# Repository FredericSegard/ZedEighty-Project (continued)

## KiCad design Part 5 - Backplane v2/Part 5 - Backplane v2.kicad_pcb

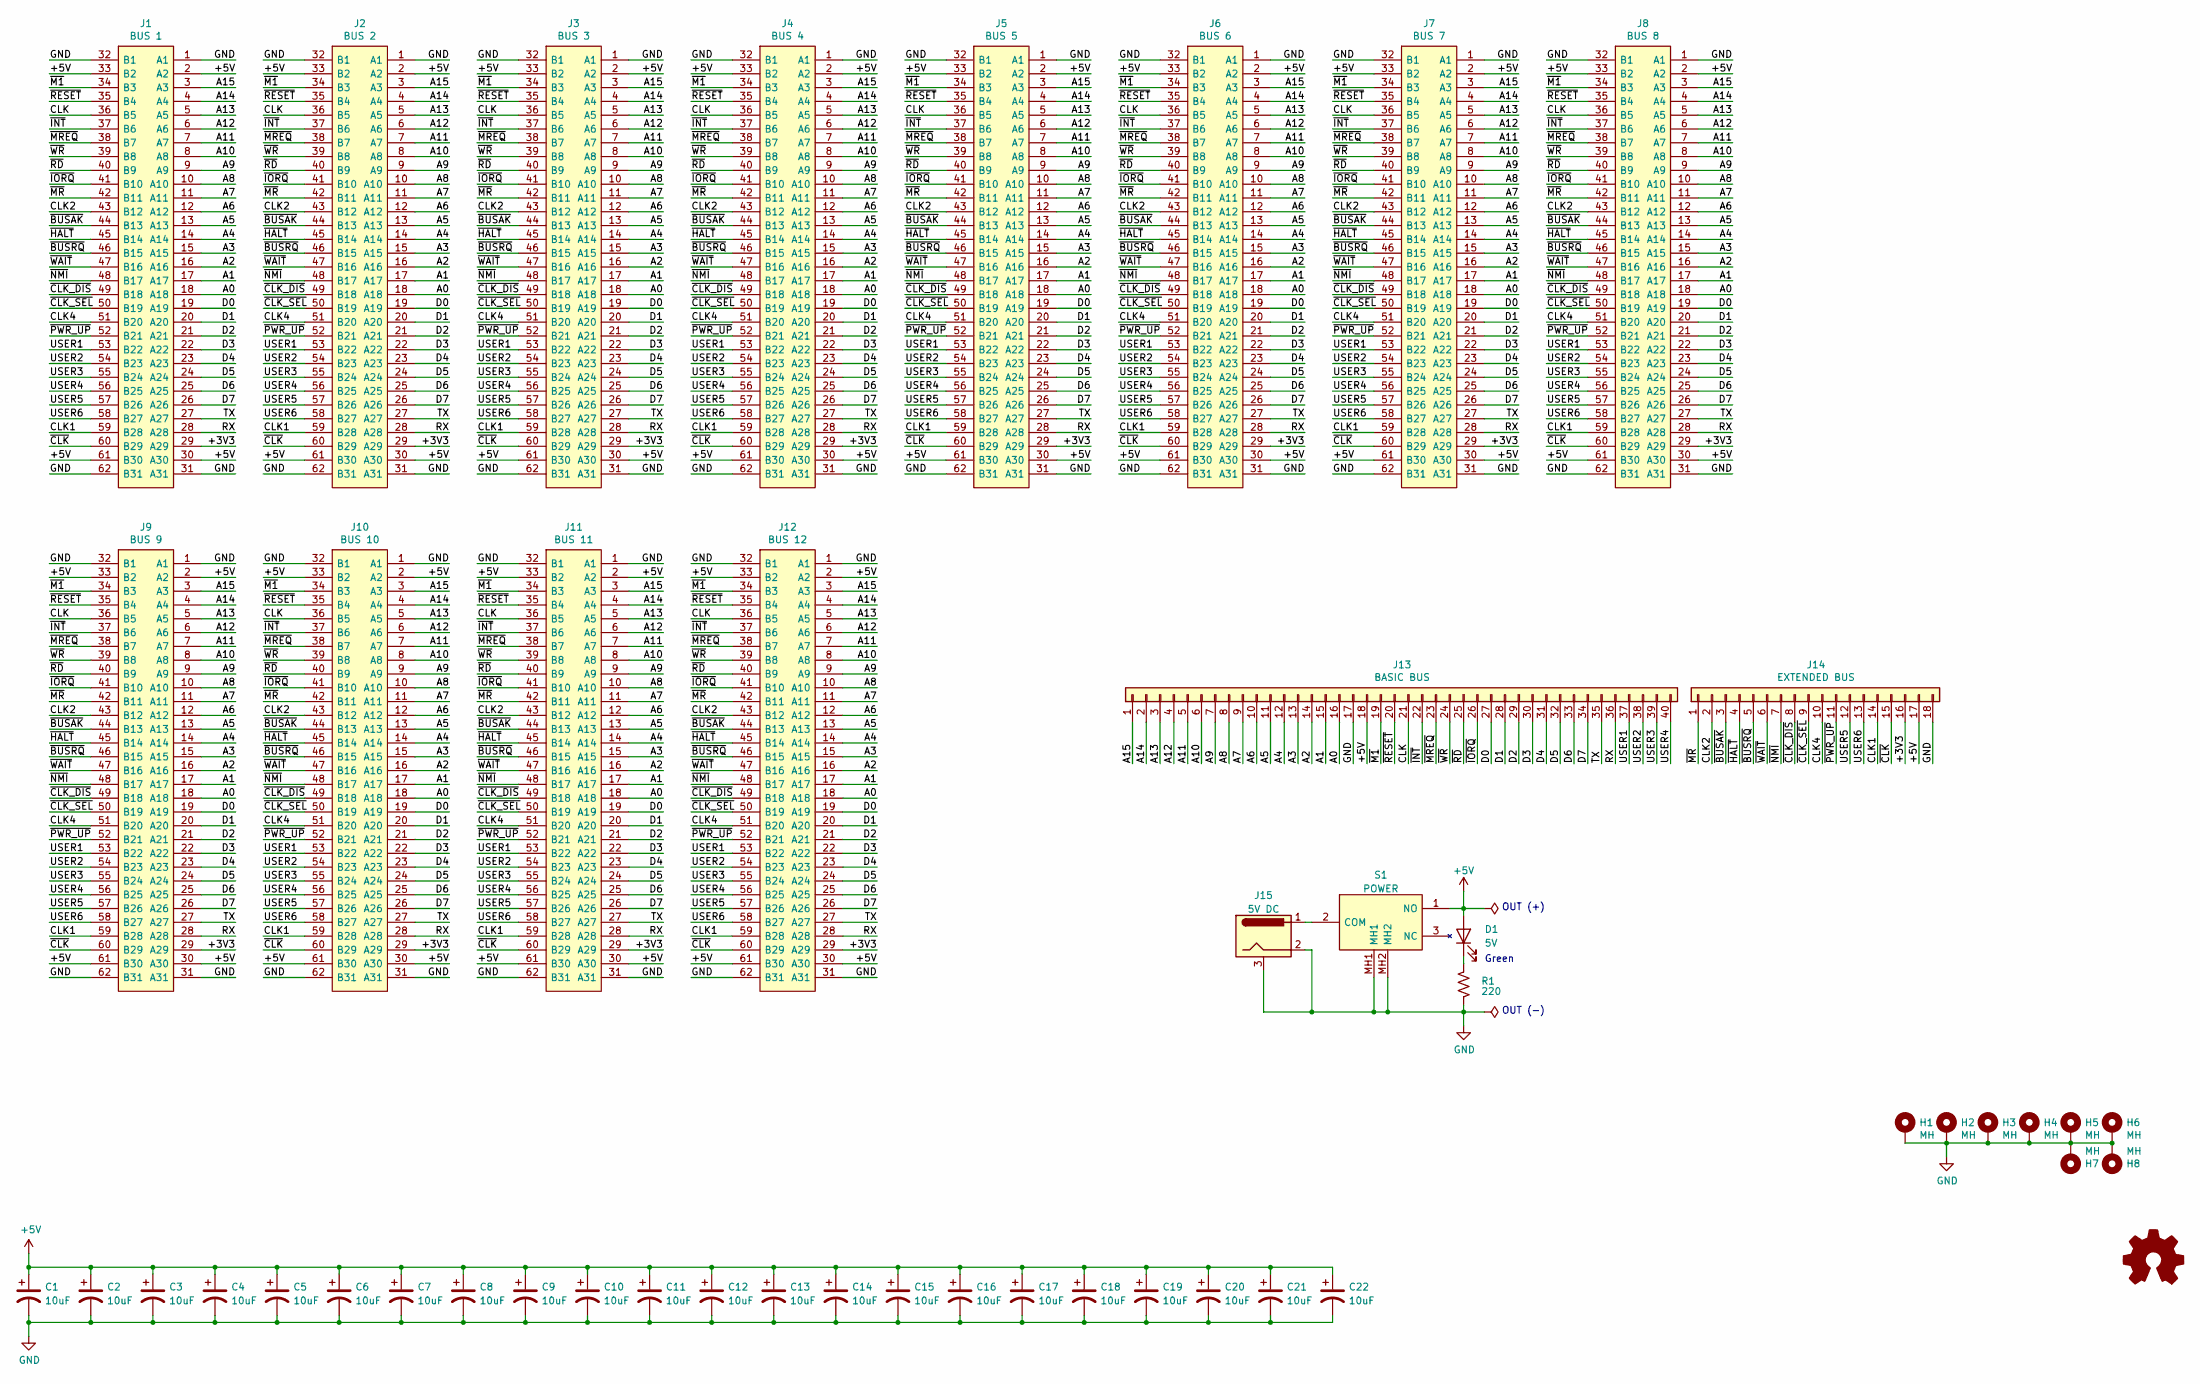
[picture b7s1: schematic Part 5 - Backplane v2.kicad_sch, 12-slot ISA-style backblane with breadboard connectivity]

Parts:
C1, C2, C3, C4, C5, C6, C7, C8, C9, C10, C11, C12, C13, C14, C15, C16, C17, C18, C19, C20, C21, C22: 10uF; CP_Radial_D6.3mm_P2.50mm
D1: 5V; LED_D3.0mm
H1, H2, H3, H4, H5, H6, H7, H8: MH; MountingHole_3.2mm_M3_Pad_Via
J1: BUS 1; ISA_Connector; Mouser Part Number 571-6-5530843-5
J2: BUS 2; ISA_Connector; Mouser Part Number 571-6-5530843-5
J3: BUS 3; ISA_Connector; Mouser Part Number 571-6-5530843-5
J4: BUS 4; ISA_Connector; Mouser Part Number 571-6-5530843-5
J5: BUS 5; ISA_Connector; Mouser Part Number 571-6-5530843-5
J6: BUS 6; ISA_Connector; Mouser Part Number 571-6-5530843-5
J7: BUS 7; ISA_Connector; Mouser Part Number 571-6-5530843-5
J8: BUS 8; ISA_Connector; Mouser Part Number 571-6-5530843-5
J9: BUS 9; ISA_Connector; Mouser Part Number 571-6-5530843-5
J10: BUS 10; ISA_Connector; Mouser Part Number 571-6-5530843-5
J11: BUS 11; ISA_Connector; Mouser Part Number 571-6-5530843-5
J12: BUS 12; ISA_Connector; Mouser Part Number 571-6-5530843-5
J13: BASIC BUS; PinHeader_1x40_P2.54mm_Vertical
J14: EXTENDED BUS; PinHeader_1x18_P2.54mm_Vertical
J15: 5V DC; BarrelJack_Horizontal
R1: 220; R_Axial_DIN0207_L6.3mm_D2.5mm_P10.16mm_Horizontal
S1: POWER; SPDT_NKK_SWITCH_M2012S2A2W30; Manufacturer_Part_Number M2012S2A2W30; Mouser Part Number 633-M2012S2A2W30

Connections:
+5V: C1.1, C2.1, C3.1, C4.1, C5.1, C6.1, C7.1, C8.1, C9.1, C10.1, C11.1, C12.1, C13.1, C14.1, C15.1, C16.1, C17.1, C18.1, C19.1, C20.1, C21.1, C22.1, D1.2 (A), J1.2 (A2), J1.30 (A30), J1.33 (B2), J1.61 (B30), J2.2 (A2), J2.30 (A30), J2.33 (B2), J2.61 (B30), J3.2 (A2), J3.30 (A30), J3.33 (B2), J3.61 (B30), J4.2 (A2), J4.30 (A30), J4.33 (B2), J4.61 (B30), J5.2 (A2), J5.30 (A30), J5.33 (B2), J5.61 (B30), J6.2 (A2), J6.30 (A30), J6.33 (B2), J6.61 (B30), J7.2 (A2), J7.30 (A30), J7.33 (B2), J7.61 (B30), J8.2 (A2), J8.30 (A30), J8.33 (B2), J8.61 (B30), J9.2 (A2), J9.30 (A30), J9.33 (B2), J9.61 (B30), J10.2 (A2), J10.30 (A30), J10.33 (B2), J10.61 (B30), J11.2 (A2), J11.30 (A30), J11.33 (B2), J11.61 (B30), J12.2 (A2), J12.30 (A30), J12.33 (B2), J12.61 (B30), J13.18, J14.17, S1.1 (NO)
/+3V3: J1.29 (A29), J2.29 (A29), J3.29 (A29), J4.29 (A29), J5.29 (A29), J6.29 (A29), J7.29 (A29), J8.29 (A29), J9.29 (A29), J10.29 (A29), J11.29 (A29), J12.29 (A29), J14.16
/A0: J1.18 (A18), J2.18 (A18), J3.18 (A18), J4.18 (A18), J5.18 (A18), J6.18 (A18), J7.18 (A18), J8.18 (A18), J9.18 (A18), J10.18 (A18), J11.18 (A18), J12.18 (A18), J13.16
/A1: J1.17 (A17), J2.17 (A17), J3.17 (A17), J4.17 (A17), J5.17 (A17), J6.17 (A17), J7.17 (A17), J8.17 (A17), J9.17 (A17), J10.17 (A17), J11.17 (A17), J12.17 (A17), J13.15
/A2: J1.16 (A16), J2.16 (A16), J3.16 (A16), J4.16 (A16), J5.16 (A16), J6.16 (A16), J7.16 (A16), J8.16 (A16), J9.16 (A16), J10.16 (A16), J11.16 (A16), J12.16 (A16), J13.14
/A3: J1.15 (A15), J2.15 (A15), J3.15 (A15), J4.15 (A15), J5.15 (A15), J6.15 (A15), J7.15 (A15), J8.15 (A15), J9.15 (A15), J10.15 (A15), J11.15 (A15), J12.15 (A15), J13.13
/A4: J1.14 (A14), J2.14 (A14), J3.14 (A14), J4.14 (A14), J5.14 (A14), J6.14 (A14), J7.14 (A14), J8.14 (A14), J9.14 (A14), J10.14 (A14), J11.14 (A14), J12.14 (A14), J13.12
/A5: J1.13 (A13), J2.13 (A13), J3.13 (A13), J4.13 (A13), J5.13 (A13), J6.13 (A13), J7.13 (A13), J8.13 (A13), J9.13 (A13), J10.13 (A13), J11.13 (A13), J12.13 (A13), J13.11
/A6: J1.12 (A12), J2.12 (A12), J3.12 (A12), J4.12 (A12), J5.12 (A12), J6.12 (A12), J7.12 (A12), J8.12 (A12), J9.12 (A12), J10.12 (A12), J11.12 (A12), J12.12 (A12), J13.10
/A7: J1.11 (A11), J2.11 (A11), J3.11 (A11), J4.11 (A11), J5.11 (A11), J6.11 (A11), J7.11 (A11), J8.11 (A11), J9.11 (A11), J10.11 (A11), J11.11 (A11), J12.11 (A11), J13.9
/A8: J1.10 (A10), J2.10 (A10), J3.10 (A10), J4.10 (A10), J5.10 (A10), J6.10 (A10), J7.10 (A10), J8.10 (A10), J9.10 (A10), J10.10 (A10), J11.10 (A10), J12.10 (A10), J13.8
/A9: J1.9 (A9), J2.9 (A9), J3.9 (A9), J4.9 (A9), J5.9 (A9), J6.9 (A9), J7.9 (A9), J8.9 (A9), J9.9 (A9), J10.9 (A9), J11.9 (A9), J12.9 (A9), J13.7
/A10: J1.8 (A8), J2.8 (A8), J3.8 (A8), J4.8 (A8), J5.8 (A8), J6.8 (A8), J7.8 (A8), J8.8 (A8), J9.8 (A8), J10.8 (A8), J11.8 (A8), J12.8 (A8), J13.6
/A11: J1.7 (A7), J2.7 (A7), J3.7 (A7), J4.7 (A7), J5.7 (A7), J6.7 (A7), J7.7 (A7), J8.7 (A7), J9.7 (A7), J10.7 (A7), J11.7 (A7), J12.7 (A7), J13.5
/A12: J1.6 (A6), J2.6 (A6), J3.6 (A6), J4.6 (A6), J5.6 (A6), J6.6 (A6), J7.6 (A6), J8.6 (A6), J9.6 (A6), J10.6 (A6), J11.6 (A6), J12.6 (A6), J13.4
/A13: J1.5 (A5), J2.5 (A5), J3.5 (A5), J4.5 (A5), J5.5 (A5), J6.5 (A5), J7.5 (A5), J8.5 (A5), J9.5 (A5), J10.5 (A5), J11.5 (A5), J12.5 (A5), J13.3
/A14: J1.4 (A4), J2.4 (A4), J3.4 (A4), J4.4 (A4), J5.4 (A4), J6.4 (A4), J7.4 (A4), J8.4 (A4), J9.4 (A4), J10.4 (A4), J11.4 (A4), J12.4 (A4), J13.2
/A15: J1.3 (A3), J2.3 (A3), J3.3 (A3), J4.3 (A3), J5.3 (A3), J6.3 (A3), J7.3 (A3), J8.3 (A3), J9.3 (A3), J10.3 (A3), J11.3 (A3), J12.3 (A3), J13.1
/CLK: J1.36 (B5), J2.36 (B5), J3.36 (B5), J4.36 (B5), J5.36 (B5), J6.36 (B5), J7.36 (B5), J8.36 (B5), J9.36 (B5), J10.36 (B5), J11.36 (B5), J12.36 (B5), J13.21
/CLK1: J1.59 (B28), J2.59 (B28), J3.59 (B28), J4.59 (B28), J5.59 (B28), J6.59 (B28), J7.59 (B28), J8.59 (B28), J9.59 (B28), J10.59 (B28), J11.59 (B28), J12.59 (B28), J14.14
/CLK2: J1.43 (B12), J2.43 (B12), J3.43 (B12), J4.43 (B12), J5.43 (B12), J6.43 (B12), J7.43 (B12), J8.43 (B12), J9.43 (B12), J10.43 (B12), J11.43 (B12), J12.43 (B12), J14.2
/CLK4: J1.51 (B20), J2.51 (B20), J3.51 (B20), J4.51 (B20), J5.51 (B20), J6.51 (B20), J7.51 (B20), J8.51 (B20), J9.51 (B20), J10.51 (B20), J11.51 (B20), J12.51 (B20), J14.10
/D0: J1.19 (A19), J2.19 (A19), J3.19 (A19), J4.19 (A19), J5.19 (A19), J6.19 (A19), J7.19 (A19), J8.19 (A19), J9.19 (A19), J10.19 (A19), J11.19 (A19), J12.19 (A19), J13.27
/D1: J1.20 (A20), J2.20 (A20), J3.20 (A20), J4.20 (A20), J5.20 (A20), J6.20 (A20), J7.20 (A20), J8.20 (A20), J9.20 (A20), J10.20 (A20), J11.20 (A20), J12.20 (A20), J13.28
/D2: J1.21 (A21), J2.21 (A21), J3.21 (A21), J4.21 (A21), J5.21 (A21), J6.21 (A21), J7.21 (A21), J8.21 (A21), J9.21 (A21), J10.21 (A21), J11.21 (A21), J12.21 (A21), J13.29
/D3: J1.22 (A22), J2.22 (A22), J3.22 (A22), J4.22 (A22), J5.22 (A22), J6.22 (A22), J7.22 (A22), J8.22 (A22), J9.22 (A22), J10.22 (A22), J11.22 (A22), J12.22 (A22), J13.30
/D4: J1.23 (A23), J2.23 (A23), J3.23 (A23), J4.23 (A23), J5.23 (A23), J6.23 (A23), J7.23 (A23), J8.23 (A23), J9.23 (A23), J10.23 (A23), J11.23 (A23), J12.23 (A23), J13.31
/D5: J1.24 (A24), J2.24 (A24), J3.24 (A24), J4.24 (A24), J5.24 (A24), J6.24 (A24), J7.24 (A24), J8.24 (A24), J9.24 (A24), J10.24 (A24), J11.24 (A24), J12.24 (A24), J13.32
/D6: J1.25 (A25), J2.25 (A25), J3.25 (A25), J4.25 (A25), J5.25 (A25), J6.25 (A25), J7.25 (A25), J8.25 (A25), J9.25 (A25), J10.25 (A25), J11.25 (A25), J12.25 (A25), J13.33
/D7: J1.26 (A26), J2.26 (A26), J3.26 (A26), J4.26 (A26), J5.26 (A26), J6.26 (A26), J7.26 (A26), J8.26 (A26), J9.26 (A26), J10.26 (A26), J11.26 (A26), J12.26 (A26), J13.34
/RX: J1.28 (A28), J2.28 (A28), J3.28 (A28), J4.28 (A28), J5.28 (A28), J6.28 (A28), J7.28 (A28), J8.28 (A28), J9.28 (A28), J10.28 (A28), J11.28 (A28), J12.28 (A28), J13.36
/TX: J1.27 (A27), J2.27 (A27), J3.27 (A27), J4.27 (A27), J5.27 (A27), J6.27 (A27), J7.27 (A27), J8.27 (A27), J9.27 (A27), J10.27 (A27), J11.27 (A27), J12.27 (A27), J13.35
/USER1: J1.53 (B22), J2.53 (B22), J3.53 (B22), J4.53 (B22), J5.53 (B22), J6.53 (B22), J7.53 (B22), J8.53 (B22), J9.53 (B22), J10.53 (B22), J11.53 (B22), J12.53 (B22), J13.37
/USER2: J1.54 (B23), J2.54 (B23), J3.54 (B23), J4.54 (B23), J5.54 (B23), J6.54 (B23), J7.54 (B23), J8.54 (B23), J9.54 (B23), J10.54 (B23), J11.54 (B23), J12.54 (B23), J13.38
/USER3: J1.55 (B24), J2.55 (B24), J3.55 (B24), J4.55 (B24), J5.55 (B24), J6.55 (B24), J7.55 (B24), J8.55 (B24), J9.55 (B24), J10.55 (B24), J11.55 (B24), J12.55 (B24), J13.39
/USER4: J1.56 (B25), J2.56 (B25), J3.56 (B25), J4.56 (B25), J5.56 (B25), J6.56 (B25), J7.56 (B25), J8.56 (B25), J9.56 (B25), J10.56 (B25), J11.56 (B25), J12.56 (B25), J13.40
/USER5: J1.57 (B26), J2.57 (B26), J3.57 (B26), J4.57 (B26), J5.57 (B26), J6.57 (B26), J7.57 (B26), J8.57 (B26), J9.57 (B26), J10.57 (B26), J11.57 (B26), J12.57 (B26), J14.12
/USER6: J1.58 (B27), J2.58 (B27), J3.58 (B27), J4.58 (B27), J5.58 (B27), J6.58 (B27), J7.58 (B27), J8.58 (B27), J9.58 (B27), J10.58 (B27), J11.58 (B27), J12.58 (B27), J14.13
/~BUSAK: J1.44 (B13), J2.44 (B13), J3.44 (B13), J4.44 (B13), J5.44 (B13), J6.44 (B13), J7.44 (B13), J8.44 (B13), J9.44 (B13), J10.44 (B13), J11.44 (B13), J12.44 (B13), J14.3
/~BUSRQ: J1.46 (B15), J2.46 (B15), J3.46 (B15), J4.46 (B15), J5.46 (B15), J6.46 (B15), J7.46 (B15), J8.46 (B15), J9.46 (B15), J10.46 (B15), J11.46 (B15), J12.46 (B15), J14.5
/~CLK_DIS: J1.49 (B18), J2.49 (B18), J3.49 (B18), J4.49 (B18), J5.49 (B18), J6.49 (B18), J7.49 (B18), J8.49 (B18), J9.49 (B18), J10.49 (B18), J11.49 (B18), J12.49 (B18), J14.8
/~CLK_SEL: J1.50 (B19), J2.50 (B19), J3.50 (B19), J4.50 (B19), J5.50 (B19), J6.50 (B19), J7.50 (B19), J8.50 (B19), J9.50 (B19), J10.50 (B19), J11.50 (B19), J12.50 (B19), J14.9
/~CLK: J1.60 (B29), J2.60 (B29), J3.60 (B29), J4.60 (B29), J5.60 (B29), J6.60 (B29), J7.60 (B29), J8.60 (B29), J9.60 (B29), J10.60 (B29), J11.60 (B29), J12.60 (B29), J14.15
/~HALT: J1.45 (B14), J2.45 (B14), J3.45 (B14), J4.45 (B14), J5.45 (B14), J6.45 (B14), J7.45 (B14), J8.45 (B14), J9.45 (B14), J10.45 (B14), J11.45 (B14), J12.45 (B14), J14.4
/~INT: J1.37 (B6), J2.37 (B6), J3.37 (B6), J4.37 (B6), J5.37 (B6), J6.37 (B6), J7.37 (B6), J8.37 (B6), J9.37 (B6), J10.37 (B6), J11.37 (B6), J12.37 (B6), J13.22
/~IORQ: J1.41 (B10), J2.41 (B10), J3.41 (B10), J4.41 (B10), J5.41 (B10), J6.41 (B10), J7.41 (B10), J8.41 (B10), J9.41 (B10), J10.41 (B10), J11.41 (B10), J12.41 (B10), J13.26
/~M1: J1.34 (B3), J2.34 (B3), J3.34 (B3), J4.34 (B3), J5.34 (B3), J6.34 (B3), J7.34 (B3), J8.34 (B3), J9.34 (B3), J10.34 (B3), J11.34 (B3), J12.34 (B3), J13.19
/~MREQ: J1.38 (B7), J2.38 (B7), J3.38 (B7), J4.38 (B7), J5.38 (B7), J6.38 (B7), J7.38 (B7), J8.38 (B7), J9.38 (B7), J10.38 (B7), J11.38 (B7), J12.38 (B7), J13.23
/~MR: J1.42 (B11), J2.42 (B11), J3.42 (B11), J4.42 (B11), J5.42 (B11), J6.42 (B11), J7.42 (B11), J8.42 (B11), J9.42 (B11), J10.42 (B11), J11.42 (B11), J12.42 (B11), J14.1
/~NMI: J1.48 (B17), J2.48 (B17), J3.48 (B17), J4.48 (B17), J5.48 (B17), J6.48 (B17), J7.48 (B17), J8.48 (B17), J9.48 (B17), J10.48 (B17), J11.48 (B17), J12.48 (B17), J14.7
/~PWR_UP: J1.52 (B21), J2.52 (B21), J3.52 (B21), J4.52 (B21), J5.52 (B21), J6.52 (B21), J7.52 (B21), J8.52 (B21), J9.52 (B21), J10.52 (B21), J11.52 (B21), J12.52 (B21), J14.11
/~RD: J1.40 (B9), J2.40 (B9), J3.40 (B9), J4.40 (B9), J5.40 (B9), J6.40 (B9), J7.40 (B9), J8.40 (B9), J9.40 (B9), J10.40 (B9), J11.40 (B9), J12.40 (B9), J13.25
/~RESET: J1.35 (B4), J2.35 (B4), J3.35 (B4), J4.35 (B4), J5.35 (B4), J6.35 (B4), J7.35 (B4), J8.35 (B4), J9.35 (B4), J10.35 (B4), J11.35 (B4), J12.35 (B4), J13.20
/~WAIT: J1.47 (B16), J2.47 (B16), J3.47 (B16), J4.47 (B16), J5.47 (B16), J6.47 (B16), J7.47 (B16), J8.47 (B16), J9.47 (B16), J10.47 (B16), J11.47 (B16), J12.47 (B16), J14.6
/~WR: J1.39 (B8), J2.39 (B8), J3.39 (B8), J4.39 (B8), J5.39 (B8), J6.39 (B8), J7.39 (B8), J8.39 (B8), J9.39 (B8), J10.39 (B8), J11.39 (B8), J12.39 (B8), J13.24
GND: C1.2, C2.2, C3.2, C4.2, C5.2, C6.2, C7.2, C8.2, C9.2, C10.2, C11.2, C12.2, C13.2, C14.2, C15.2, C16.2, C17.2, C18.2, C19.2, C20.2, C21.2, C22.2, H1.1, H2.1, H3.1, H4.1, H5.1, H6.1, H7.1, H8.1, J1.1 (A1), J1.31 (A31), J1.32 (B1), J1.62 (B31), J2.1 (A1), J2.31 (A31), J2.32 (B1), J2.62 (B31), J3.1 (A1), J3.31 (A31), J3.32 (B1), J3.62 (B31), J4.1 (A1), J4.31 (A31), J4.32 (B1), J4.62 (B31), J5.1 (A1), J5.31 (A31), J5.32 (B1), J5.62 (B31), J6.1 (A1), J6.31 (A31), J6.32 (B1), J6.62 (B31), J7.1 (A1), J7.31 (A31), J7.32 (B1), J7.62 (B31), J8.1 (A1), J8.31 (A31), J8.32 (B1), J8.62 (B31), J9.1 (A1), J9.31 (A31), J9.32 (B1), J9.62 (B31), J10.1 (A1), J10.31 (A31), J10.32 (B1), J10.62 (B31), J11.1 (A1), J11.31 (A31), J11.32 (B1), J11.62 (B31), J12.1 (A1), J12.31 (A31), J12.32 (B1), J12.62 (B31), J13.17, J14.18, J15.2, J15.3, R1.1, S1.MH1, S1.MH2
unnamed: D1.1 (K), R1.2
unnamed: J15.1, S1.2 (COM)

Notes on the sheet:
OUT (+)
Green
OUT (-)

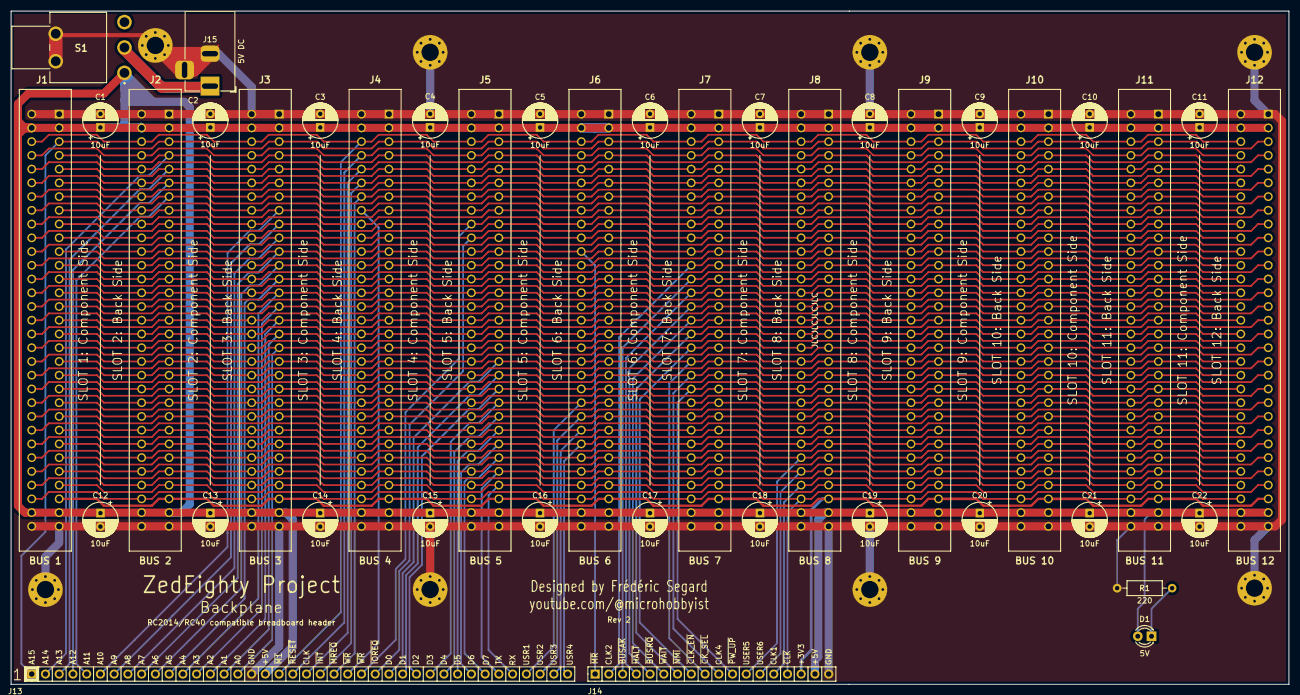
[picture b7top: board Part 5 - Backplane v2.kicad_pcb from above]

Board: 2 copper layers, 236.2 x 124.5 mm, 48 parts (0 on the bottom side), 58 nets.

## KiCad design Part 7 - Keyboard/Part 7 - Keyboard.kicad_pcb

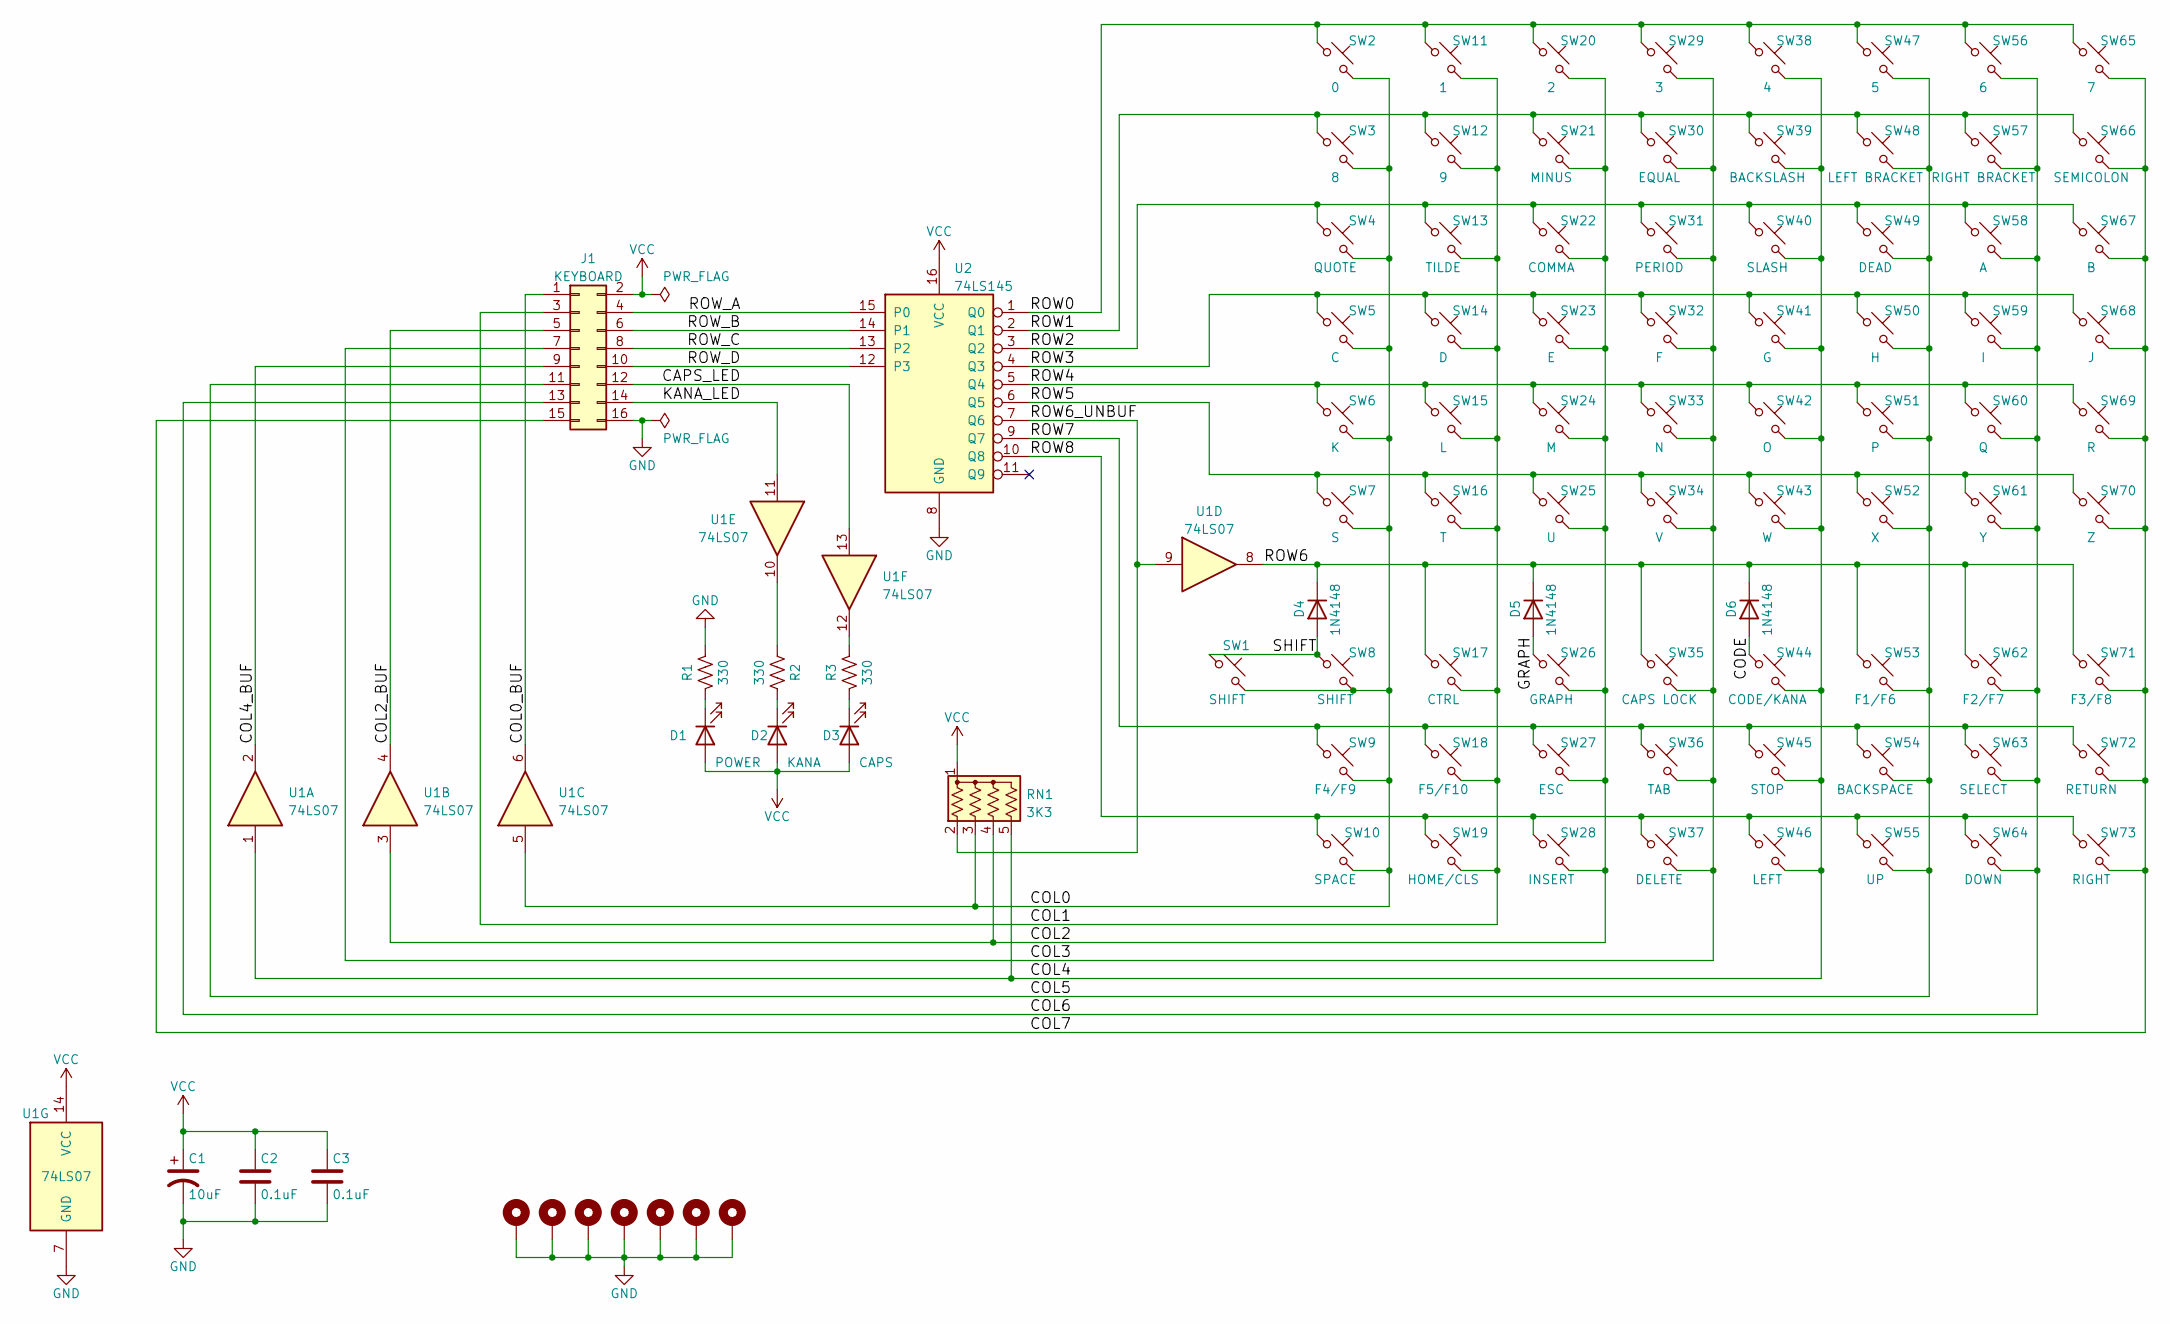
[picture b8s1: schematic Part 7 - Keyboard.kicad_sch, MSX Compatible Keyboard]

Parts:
C1: 10uF; CP_Radial_D5.0mm_P2.50mm
C2, C3: 0.1uF; C_Disc_D3.0mm_W2.0mm_P2.50mm
D1: POWER; LED_D3.0mm
D2: KANA; LED_D3.0mm
D3: CAPS; LED_D3.0mm
D4, D5, D6: 1N4148; D_DO-35_SOD27_P7.62mm_Horizontal
H1: MH; MountingHole_3.2mm_M3_Pad_Via
H2, H3, H4, H5, H6, H7: MountingHole_Pad; MountingHole_3.2mm_M3_Pad_Via
J1: KEYBOARD; PinSocket_2x08_P2.54mm_Vertical
R1, R2, R3: 330; R_Axial_DIN0204_L3.6mm_D1.6mm_P7.62mm_Horizontal
RN1: 3K3; R_Array_SIP5
SW1: SHIFT; SW_Cherry_MX_2.75u_PCB
SW2: 0; SW_Cherry_MX_1.00u_PCB
SW3: 8; SW_Cherry_MX_1.00u_PCB
SW4: QUOTE; SW_Cherry_MX_1.00u_PCB
SW5: C; SW_Cherry_MX_1.00u_PCB
SW6: K; SW_Cherry_MX_1.00u_PCB
SW7: S; SW_Cherry_MX_1.00u_PCB
SW8: SHIFT; SW_Cherry_MX_2.25u_PCB
SW9: F4/F9; SW_Cherry_MX_1.00u_PCB
SW10: SPACE; SW_Cherry_MX_6.25u_PCB
SW11: 1; SW_Cherry_MX_1.00u_PCB
SW12: 9; SW_Cherry_MX_1.00u_PCB
SW13: TILDE; SW_Cherry_MX_1.00u_PCB
SW14: D; SW_Cherry_MX_1.00u_PCB
SW15: L; SW_Cherry_MX_1.00u_PCB
SW16: T; SW_Cherry_MX_1.00u_PCB
SW17: CTRL; SW_Cherry_MX_1.25u_PCB
SW18: F5/F10; SW_Cherry_MX_1.00u_PCB
SW19: HOME/CLS; SW_Cherry_MX_1.00u_PCB
SW20: 2; SW_Cherry_MX_1.00u_PCB
SW21: MINUS; SW_Cherry_MX_1.00u_PCB
SW22: COMMA; SW_Cherry_MX_1.00u_PCB
SW23: E; SW_Cherry_MX_1.00u_PCB
SW24: M; SW_Cherry_MX_1.00u_PCB
SW25: U; SW_Cherry_MX_1.00u_PCB
SW26: GRAPH; SW_Cherry_MX_1.25u_PCB
SW27: ESC; SW_Cherry_MX_1.00u_PCB
SW28: INSERT; SW_Cherry_MX_1.00u_PCB
SW29: 3; SW_Cherry_MX_1.00u_PCB
SW30: EQUAL; SW_Cherry_MX_1.00u_PCB
SW31: PERIOD; SW_Cherry_MX_1.00u_PCB
SW32: F; SW_Cherry_MX_1.00u_PCB
SW33: N; SW_Cherry_MX_1.00u_PCB
SW34: V; SW_Cherry_MX_1.00u_PCB
SW35: CAPS LOCK; SW_Cherry_MX_1.75u_PCB
SW36: TAB; SW_Cherry_MX_1.50u_PCB
SW37: DELETE; SW_Cherry_MX_1.00u_PCB
SW38: 4; SW_Cherry_MX_1.00u_PCB
SW39: BACKSLASH; SW_Cherry_MX_1.50u_PCB
SW40: SLASH; SW_Cherry_MX_1.00u_PCB
SW41: G; SW_Cherry_MX_1.00u_PCB
SW42: O; SW_Cherry_MX_1.00u_PCB
SW43: W; SW_Cherry_MX_1.00u_PCB
SW44: CODE/KANA; SW_Cherry_MX_1.25u_PCB
SW45: STOP; SW_Cherry_MX_1.00u_PCB
SW46: LEFT; SW_Cherry_MX_1.00u_PCB
SW47: 5; SW_Cherry_MX_1.00u_PCB
SW48: LEFT BRACKET; SW_Cherry_MX_1.00u_PCB
SW49: DEAD; SW_Cherry_MX_1.25u_PCB
SW50: H; SW_Cherry_MX_1.00u_PCB
SW51: P; SW_Cherry_MX_1.00u_PCB
SW52: X; SW_Cherry_MX_1.00u_PCB
SW53: F1/F6; SW_Cherry_MX_1.00u_PCB
SW54: BACKSPACE; SW_Cherry_MX_2.00u_PCB
SW55: UP; SW_Cherry_MX_1.00u_PCB
SW56: 6; SW_Cherry_MX_1.00u_PCB
SW57: RIGHT BRACKET; SW_Cherry_MX_1.00u_PCB
SW58: A; SW_Cherry_MX_1.00u_PCB
SW59: I; SW_Cherry_MX_1.00u_PCB
SW60: Q; SW_Cherry_MX_1.00u_PCB
SW61: Y; SW_Cherry_MX_1.00u_PCB
SW62: F2/F7; SW_Cherry_MX_1.00u_PCB
SW63: SELECT; SW_Cherry_MX_1.25u_PCB
SW64: DOWN; SW_Cherry_MX_1.00u_PCB
SW65: 7; SW_Cherry_MX_1.00u_PCB
SW66: SEMICOLON; SW_Cherry_MX_1.00u_PCB
SW67: B; SW_Cherry_MX_1.00u_PCB
SW68: J; SW_Cherry_MX_1.00u_PCB
SW69: R; SW_Cherry_MX_1.00u_PCB
SW70: Z; SW_Cherry_MX_1.00u_PCB
SW71: F3/F8; SW_Cherry_MX_1.00u_PCB
SW72: RETURN; SW_Cherry_MX_2.25u_PCB
SW73: RIGHT; SW_Cherry_MX_1.00u_PCB
U1: 74LS07; DIP-14_W7.62mm_Socket
U2: 74LS145; DIP-16_W7.62mm_Socket

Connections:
/CAPS_LED: J1.12, U1.13
/CODE: D6.2 (A), SW44.1
/COL0: RN1.3 (R2), SW1.2, SW2.2, SW3.2, SW4.2, SW5.2, SW6.2, SW7.2, SW8.2, SW9.2, SW10.2, U1.5
/COL0_BUF: J1.1, U1.6
/COL1: J1.3, SW11.2, SW12.2, SW13.2, SW14.2, SW15.2, SW16.2, SW17.2, SW18.2, SW19.2
/COL2: RN1.4 (R3), SW20.2, SW21.2, SW22.2, SW23.2, SW24.2, SW25.2, SW26.2, SW27.2, SW28.2, U1.3
/COL2_BUF: J1.5, U1.4
/COL3: J1.7, SW29.2, SW30.2, SW31.2, SW32.2, SW33.2, SW34.2, SW35.2, SW36.2, SW37.2
/COL4: RN1.5 (R4), SW38.2, SW39.2, SW40.2, SW41.2, SW42.2, SW43.2, SW44.2, SW45.2, SW46.2, U1.1
/COL4_BUF: J1.9, U1.2
/COL5: J1.11, SW47.2, SW48.2, SW49.2, SW50.2, SW51.2, SW52.2, SW53.2, SW54.2, SW55.2
/COL6: J1.13, SW56.2, SW57.2, SW58.2, SW59.2, SW60.2, SW61.2, SW62.2, SW63.2, SW64.2
/COL7: J1.15, SW65.2, SW66.2, SW67.2, SW68.2, SW69.2, SW70.2, SW71.2, SW72.2, SW73.2
/GRAPH: D5.2 (A), SW26.1
/KANA_LED: J1.14, U1.11
/ROW0: SW2.1, SW11.1, SW20.1, SW29.1, SW38.1, SW47.1, SW56.1, SW65.1, U2.1 (Q0)
/ROW1: SW3.1, SW12.1, SW21.1, SW30.1, SW39.1, SW48.1, SW57.1, SW66.1, U2.2 (Q1)
/ROW2: SW4.1, SW13.1, SW22.1, SW31.1, SW40.1, SW49.1, SW58.1, SW67.1, U2.3 (Q2)
/ROW3: SW5.1, SW14.1, SW23.1, SW32.1, SW41.1, SW50.1, SW59.1, SW68.1, U2.4 (Q3)
/ROW4: SW6.1, SW15.1, SW24.1, SW33.1, SW42.1, SW51.1, SW60.1, SW69.1, U2.5 (Q4)
/ROW5: SW7.1, SW16.1, SW25.1, SW34.1, SW43.1, SW52.1, SW61.1, SW70.1, U2.6 (Q5)
/ROW6: D4.1 (K), D5.1 (K), D6.1 (K), SW17.1, SW35.1, SW53.1, SW62.1, SW71.1, U1.8
/ROW6_UNBUF: RN1.2 (R1), U1.9, U2.7 (Q6)
/ROW7: SW9.1, SW18.1, SW27.1, SW36.1, SW45.1, SW54.1, SW63.1, SW72.1, U2.9 (Q7)
/ROW8: SW10.1, SW19.1, SW28.1, SW37.1, SW46.1, SW55.1, SW64.1, SW73.1, U2.10 (Q8)
/ROW_A: J1.4, U2.15 (P0)
/ROW_B: J1.6, U2.14 (P1)
/ROW_C: J1.8, U2.13 (P2)
/ROW_D: J1.10, U2.12 (P3)
/SHIFT: D4.2 (A), SW1.1, SW8.1
GND: C1.2, C2.2, C3.2, H1.1, H2.1, H3.1, H4.1, H5.1, H6.1, H7.1, J1.16, R1.1, U1.7 (GND), U2.8 (GND)
unnamed: D1.1 (K), R1.2
unnamed: D2.1 (K), R2.2
unnamed: D3.1 (K), R3.2
unnamed: R2.1, U1.10
unnamed: R3.1, U1.12
VCC: C1.1, C2.1, C3.1, D1.2 (A), D2.2 (A), D3.2 (A), J1.2, RN1.1 (common), U1.14 (VCC), U2.16 (VCC)

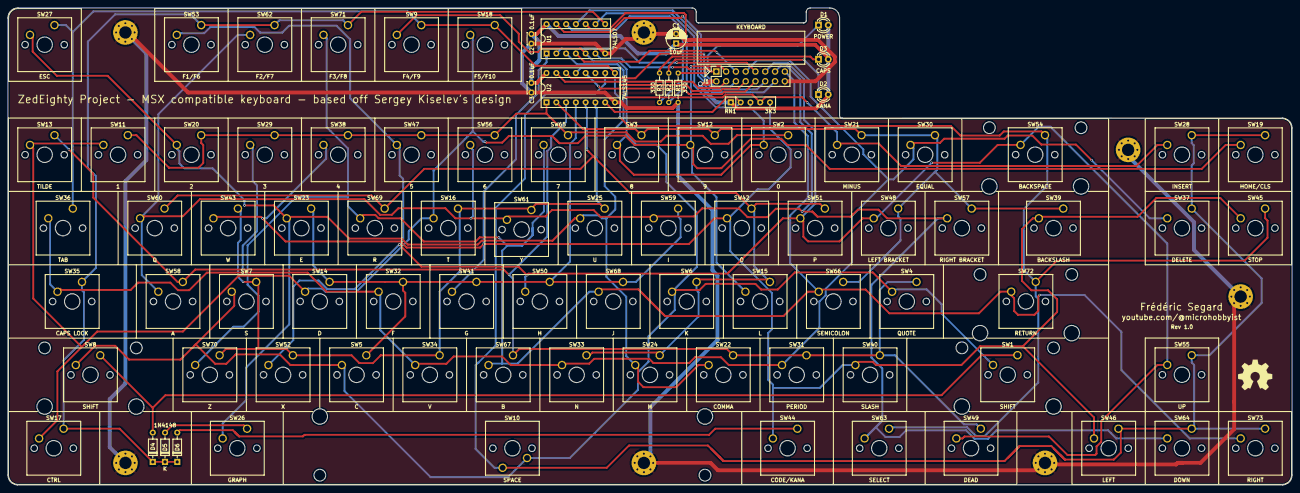
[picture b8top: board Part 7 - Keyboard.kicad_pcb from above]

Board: 2 copper layers, 333.4 x 123.8 mm, 98 parts (1 on the bottom side), 37 nets.

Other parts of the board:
REF3, REF4: OSHW-Symbol_8.9x8mm_SilkScreen

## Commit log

2022-09-30 Updating resistor values and added PDF schematic
2022-09-30 Removing old backups
2022-09-30 Removed backup files
2022-09-30 Added Part 2, and part of Part 3
2022-09-30 Worked on Part 3's clock
2022-10-03 Finished clock in part 2, added part 3
2022-10-03 Updated glue logic and bank switching
2022-10-14 Backplane PCB sent out, and experimented with clock options
2022-10-21 Added software selectable speed control
2022-10-28 Updated clock, and created CPU card
2022-11-01 Changed the clock for even cleaner clock switching
2022-11-01 Attempted to reduce chip count
2022-11-07 Clock 3 and Keyboard
2022-11-30 Added Keyboard, and minor fixes
2022-12-04 Updated key library and keyboard
2023-01-05 Long time backup
